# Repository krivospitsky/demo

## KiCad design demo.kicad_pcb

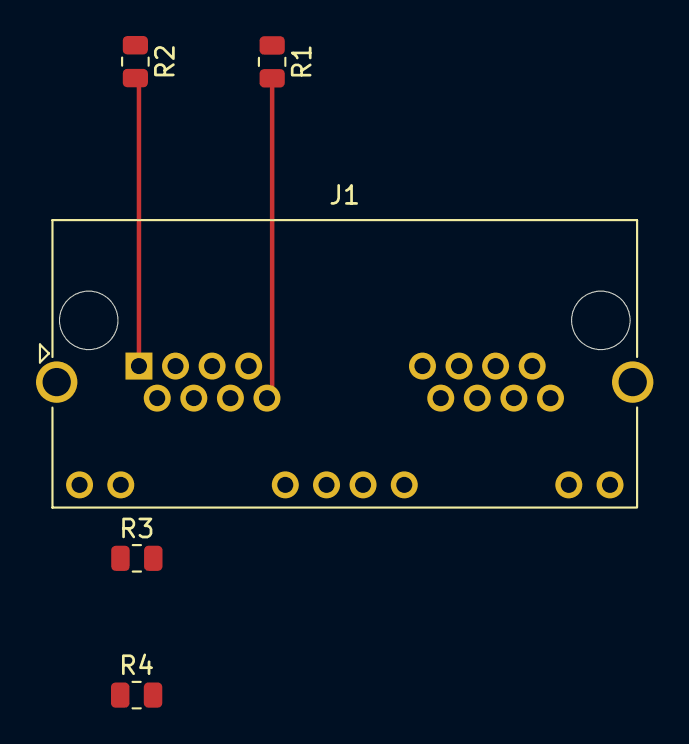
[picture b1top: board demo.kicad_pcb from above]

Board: 2 copper layers, 5 parts (0 on the bottom side), 6 nets.

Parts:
J1: 8P8C_LED_Shielded_x2; RJ45_Amphenol_RJHSE538X-02
R1, R2, R3, R4: R; R_0805_2012Metric

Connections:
+3.3V: R1.1, R3.1
GND: R2.1, R4.1
unnamed: J1.1, R2.2
unnamed: J1.8, R1.2
unnamed: J1.13, R4.2
unnamed: J1.20, R3.2

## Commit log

2022-10-10 init
